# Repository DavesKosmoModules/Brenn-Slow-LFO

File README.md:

# Brenn-Slow-LFO

100mm Quad Slow LFO

- 4 Lfo's
- Each has a cycle duration between a few seconds and a few minutes, approx 6 sec 12 minutes
- Each LFO has it's own speed control
- A single global speed control
- CV control for the global speed (not 1V/Oct)
- Each LFO has both unipolar and bipolar outputs

I have been using the lfo for slow evolving movement of sounds, it is not a replacement for a standard lfo, normal tremolo
and vibrato can not be realized with this module.

It is based on the single cell VCO on the LM13700 datasheet, this is a triangle wave with a big step so I added
a LPF to each oscillator.

Contained are schematics & gerber files for pcb fabrication of both electrical aux and front panel. This is sutiable for entry level however a basic level of electronics, soldering, fault finding, and some basic tools are required.

[Schematic](/Docs/Brenn-Schematic.pdf)

[BOM](Docs/Brenn-BOM.pdf)

If you wish to edit in ki-cad the following dependencies are required

 https://github.com/holmesrichards/Kosmo_panel
 
 https://github.com/holmesrichards/aoKicad

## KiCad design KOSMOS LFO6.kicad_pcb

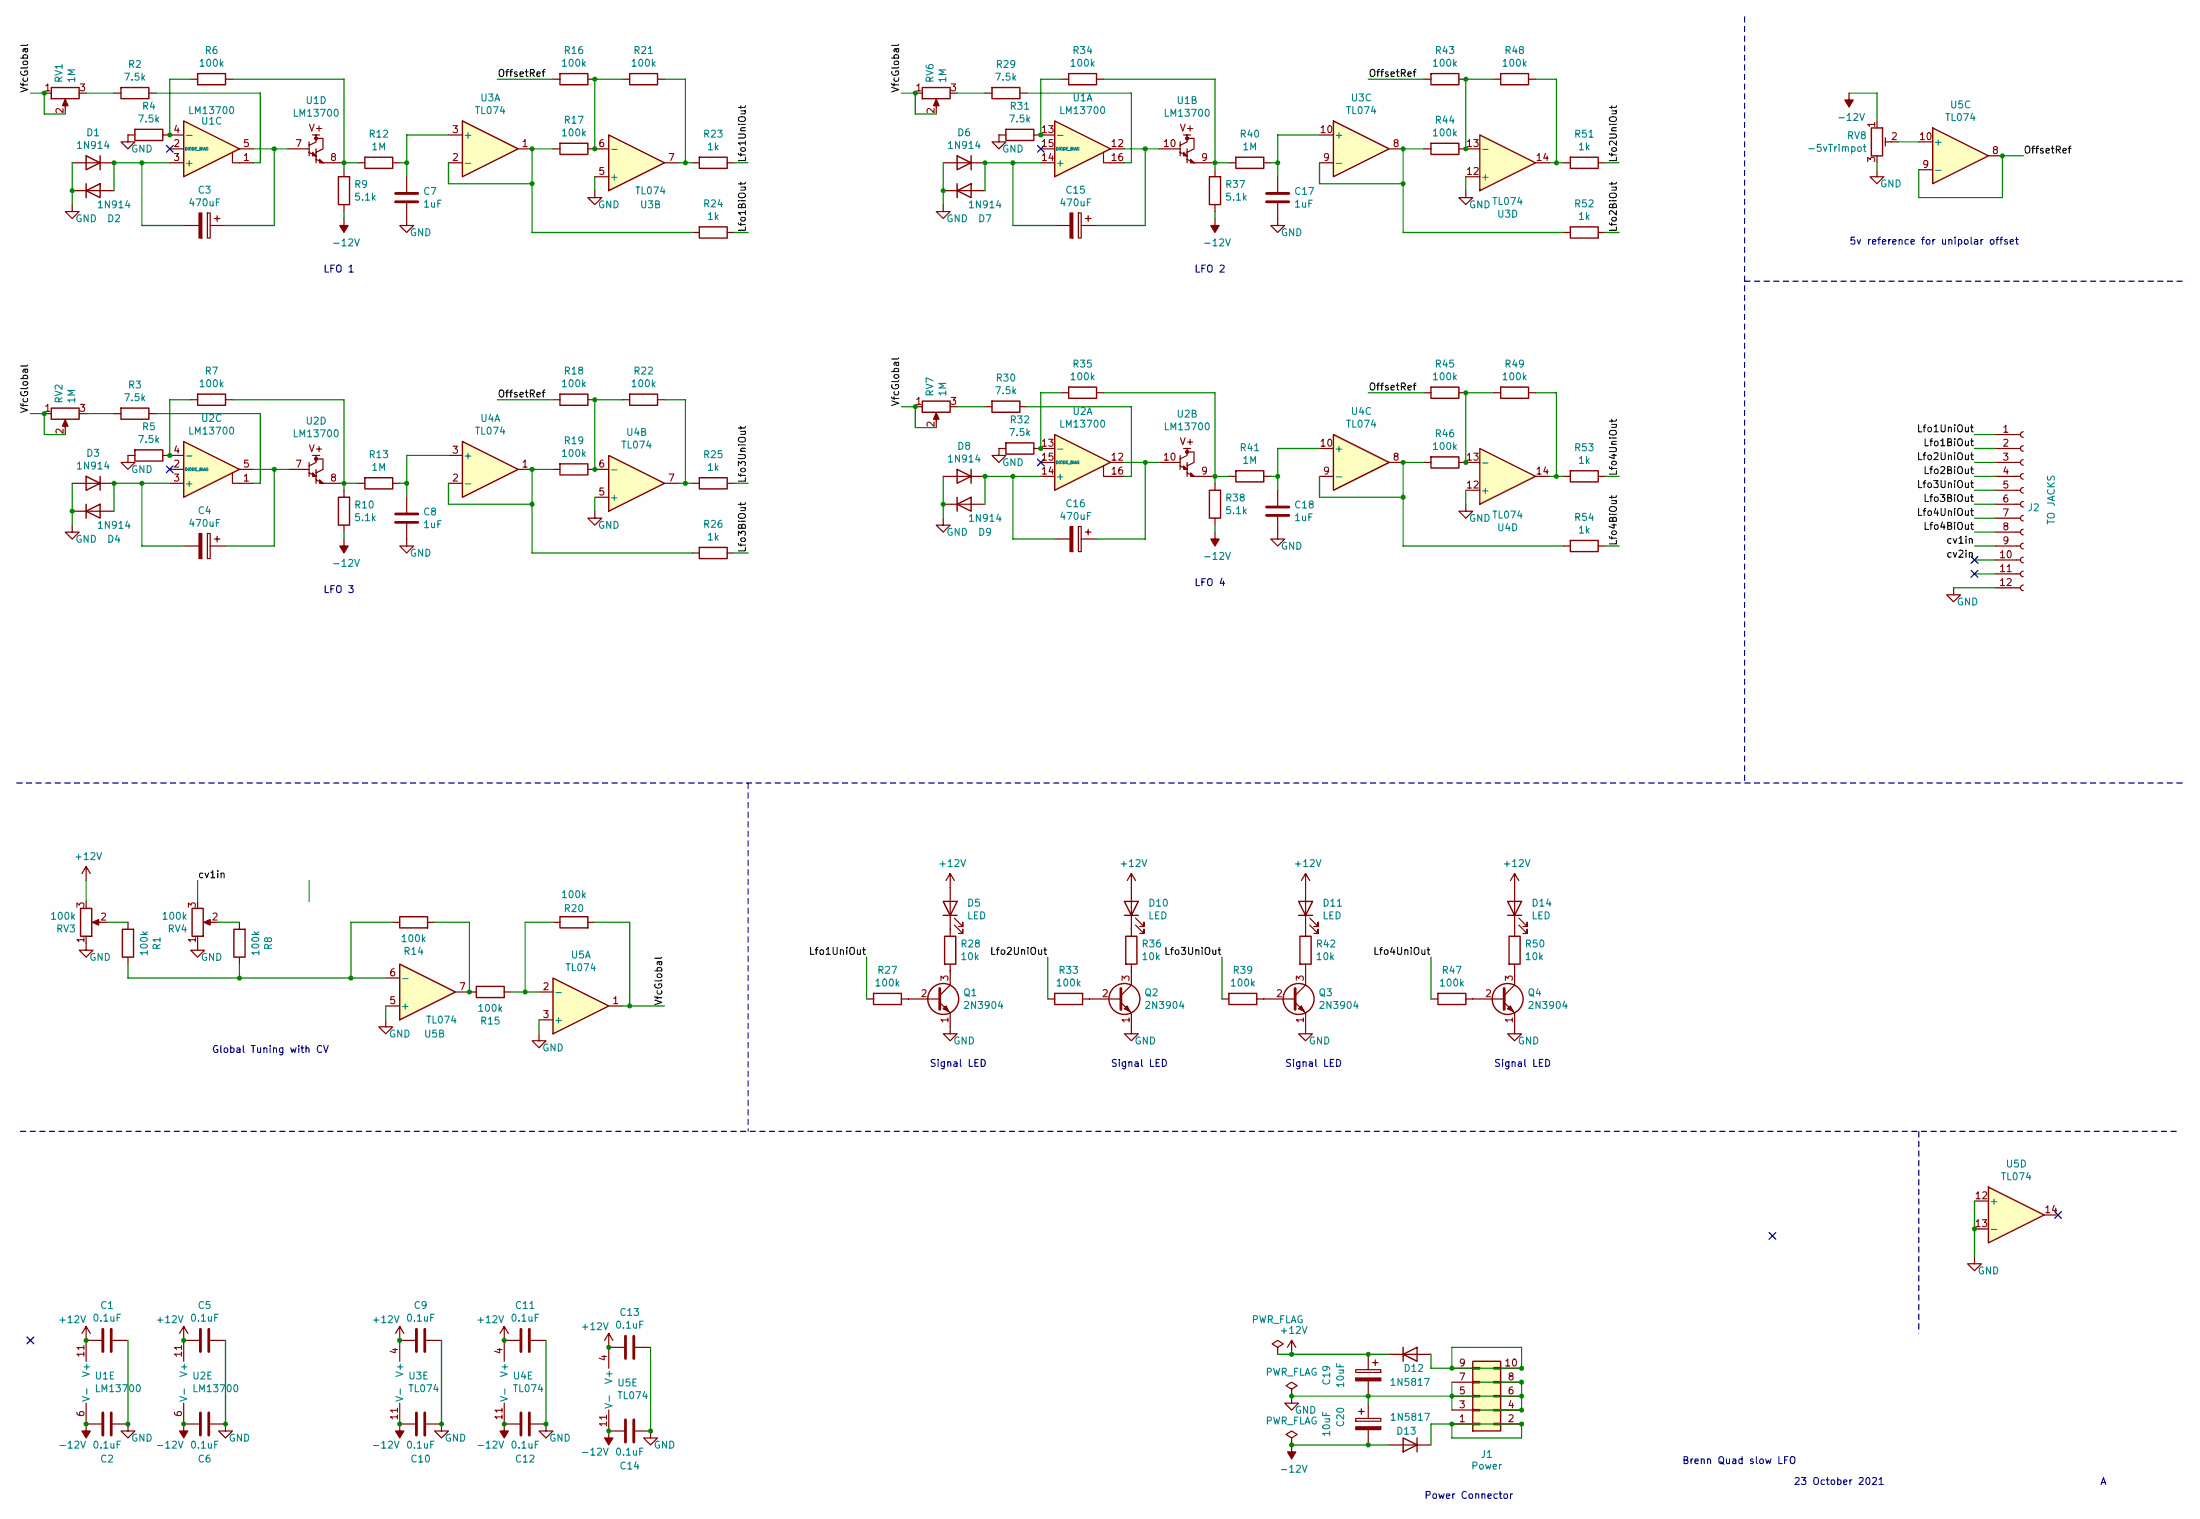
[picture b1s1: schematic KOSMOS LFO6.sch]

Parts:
C1, C2, C5, C6, C9, C10, C11, C12, C13, C14: 0.1uF; C_Disc_D6.0mm_W4.4mm_P5.00mm
C3, C4, C15, C16: 470uF; CP_Radial_D7.5mm_P2.50mm
C7, C8, C17, C18: 1uF; C_Disc_D6.0mm_W4.4mm_P5.00mm
C19, C20: 10uF; CP_Radial_D7.5mm_P2.50mm
D1, D2, D3, D4, D6, D7, D8, D9: 1N914; D_DO-35_SOD27_P7.62mm_Horizontal
D5, D10, D11, D14: LED; LED_D5.0mm
D12, D13: 1N5817; D_DO-41_SOD81_P12.70mm_Horizontal
J1: Power; IDC-Header_2x05_P2.54mm_Vertical
J2: TO JACKS; PinSocket_1x12_P2.54mm_Vertical
Q1, Q2, Q3, Q4: 2N3904; TO-92_Inline_Wide
R1, R6, R7, R8, R14, R15, R16, R17, R18, R19, R20, R21, R22, R27, R33, R34, R35, R39, R43, R44, R45, R46, R47, R48, R49: 100k; R_Axial_DIN0207_L6.3mm_D2.5mm_P10.16mm_Horizontal
R2, R3, R4, R5, R29, R30, R31, R32: 7.5k; R_Axial_DIN0207_L6.3mm_D2.5mm_P10.16mm_Horizontal
R9, R10, R37, R38: 5.1k; R_Axial_DIN0207_L6.3mm_D2.5mm_P10.16mm_Horizontal
R12, R13, R40, R41: 1M; R_Axial_DIN0207_L6.3mm_D2.5mm_P10.16mm_Horizontal
R23, R24, R25, R26, R51, R52, R53, R54: 1k; R_Axial_DIN0207_L6.3mm_D2.5mm_P10.16mm_Horizontal
R28, R36, R42, R50: 10k; R_Axial_DIN0207_L6.3mm_D2.5mm_P10.16mm_Horizontal
RV1, RV2, RV6, RV7: 1M; Potentiometer_Alpha_RD901F-40-00D_Single_Vertical_CircularH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
RV3, RV4: 100k; Potentiometer_Alpha_RD901F-40-00D_Single_Vertical_CircularH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
RV8: -5vTrimpot; Potentiometer_Bourns_3299W_Vertical
U1, U2: LM13700; DIP-16_W7.62mm_LongPads
U3, U4, U5: TL074; DIP-14_W7.62mm_LongPads

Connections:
+12V: C1.2, C5.2, C9.2, C11.2, C13.2, C19.1, D5.2 (A), D10.2 (A), D11.2 (A), D12.1 (K), D14.2 (A), RV3.3, U1.11 (V+), U2.11 (V+), U3.4 (V+), U4.4 (V+), U5.4 (V+)
-12V: C2.2, C6.2, C10.2, C12.2, C14.2, C20.2, D13.2 (A), R9.1, R10.1, R37.1, R38.1, RV8.1, U1.6 (V-), U2.6 (V-), U3.11 (V-), U4.11 (V-), U5.11 (V-)
/Lfo1BiOut: J2.2, R24.1
/Lfo1UniOut: J2.1, R23.1, R27.2
/Lfo2BiOut: J2.4, R52.1
/Lfo2UniOut: J2.3, R33.2, R51.1
/Lfo3BiOut: J2.6, R26.1
/Lfo3UniOut: J2.5, R25.1, R39.2
/Lfo4BiOut: J2.8, R54.1
/Lfo4UniOut: J2.7, R47.2, R53.1
/OffsetRef: R16.2, R18.2, R43.2, R45.2, U5.8, U5.9 (-)
/VfcGlobal: R20.2, RV1.1, RV1.2, RV2.1, RV2.2, RV6.1, RV6.2, RV7.1, RV7.2, U5.1
/cv1in: J2.9, RV4.3
/cv2in: J2.10
GND: C1.1, C2.1, C5.1, C6.1, C7.2, C8.2, C9.1, C10.1, C11.1, C12.1, C13.1, C14.1, C17.2, C18.2, C19.2, C20.1, D1.2 (A), D2.1 (K), D3.2 (A), D4.1 (K), D6.2 (A), D7.1 (K), D8.2 (A), D9.1 (K), J1.3, J1.4, J1.5, J1.6, J1.7, J1.8, J2.12, Q1.1 (E), Q2.1 (E), Q3.1 (E), Q4.1 (E), R4.2, R5.2, R31.2, R32.2, RV3.1, RV4.1, RV8.3, U3.5 (+), U3.12 (+), U4.5 (+), U4.12 (+), U5.3 (+), U5.5 (+), U5.12 (+), U5.13 (-)
unnamed: C3.1, U1.5, U1.7
unnamed: C3.2, D1.1 (K), D2.2 (A), U1.3 (+)
unnamed: C4.1, U2.5, U2.7
unnamed: C4.2, D3.1 (K), D4.2 (A), U2.3 (+)
unnamed: C7.1, R12.1, U3.3 (+)
unnamed: C8.1, R13.1, U4.3 (+)
unnamed: C15.1, U1.10, U1.12
unnamed: C15.2, D6.1 (K), D7.2 (A), U1.14 (+)
unnamed: C16.1, U2.10, U2.12
unnamed: C16.2, D8.1 (K), D9.2 (A), U2.14 (+)
unnamed: C17.1, R40.1, U3.10 (+)
unnamed: C18.1, R41.1, U4.10 (+)
unnamed: D5.1 (K), R28.1
unnamed: D10.1 (K), R36.1
unnamed: D11.1 (K), R42.1
unnamed: D12.2 (A), J1.9, J1.10
unnamed: D13.1 (K), J1.1, J1.2
unnamed: D14.1 (K), R50.1
unnamed: Q1.2 (B), R27.1
unnamed: Q1.3 (C), R28.2
unnamed: Q2.2 (B), R33.1
unnamed: Q2.3 (C), R36.2
unnamed: Q3.2 (B), R39.1
unnamed: Q3.3 (C), R42.2
unnamed: Q4.2 (B), R47.1
unnamed: Q4.3 (C), R50.2
unnamed: R1.1, R8.1, R14.1, U5.6 (-)
unnamed: R1.2, RV3.2
unnamed: R2.1, U1.1
unnamed: R2.2, RV1.3
unnamed: R3.1, U2.1
unnamed: R3.2, RV2.3
unnamed: R4.1, R6.2, U1.4 (-)
unnamed: R5.1, R7.2, U2.4 (-)
unnamed: R8.2, RV4.2
unnamed: R7.1, R10.2, R13.2, U2.8
unnamed: R6.1, R9.2, R12.2, U1.8
unnamed: R14.2, R15.1, U5.7
unnamed: R15.2, R20.1, U5.2 (-)
unnamed: R16.1, R17.1, R21.2, U3.6 (-)
unnamed: R17.2, R24.2, U3.1, U3.2 (-)
unnamed: R18.1, R19.1, R22.2, U4.6 (-)
unnamed: R19.2, R26.2, U4.1, U4.2 (-)
unnamed: R21.1, R23.2, U3.7
unnamed: R22.1, R25.2, U4.7
unnamed: R29.1, U1.16
unnamed: R29.2, RV6.3
unnamed: R30.1, U2.16
unnamed: R30.2, RV7.3
unnamed: R31.1, R34.2, U1.13 (-)
unnamed: R32.1, R35.2, U2.13 (-)
unnamed: R34.1, R37.2, R40.2, U1.9
unnamed: R35.1, R38.2, R41.2, U2.9
unnamed: R43.1, R44.1, R48.2, U3.13 (-)
unnamed: R44.2, R52.2, U3.8, U3.9 (-)
unnamed: R45.1, R46.1, R49.2, U4.13 (-)
unnamed: R46.2, R54.2, U4.8, U4.9 (-)
unnamed: R48.1, R51.2, U3.14
unnamed: R49.1, R53.2, U4.14
unnamed: RV8.2, U5.10 (+)

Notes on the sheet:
Power Connector
Signal LED
LFO 1
LFO 2
LFO 3
LFO 4
Global Tuning with CV
5v reference for unipolar offset
23 October 2021
Brenn Quad slow LFO

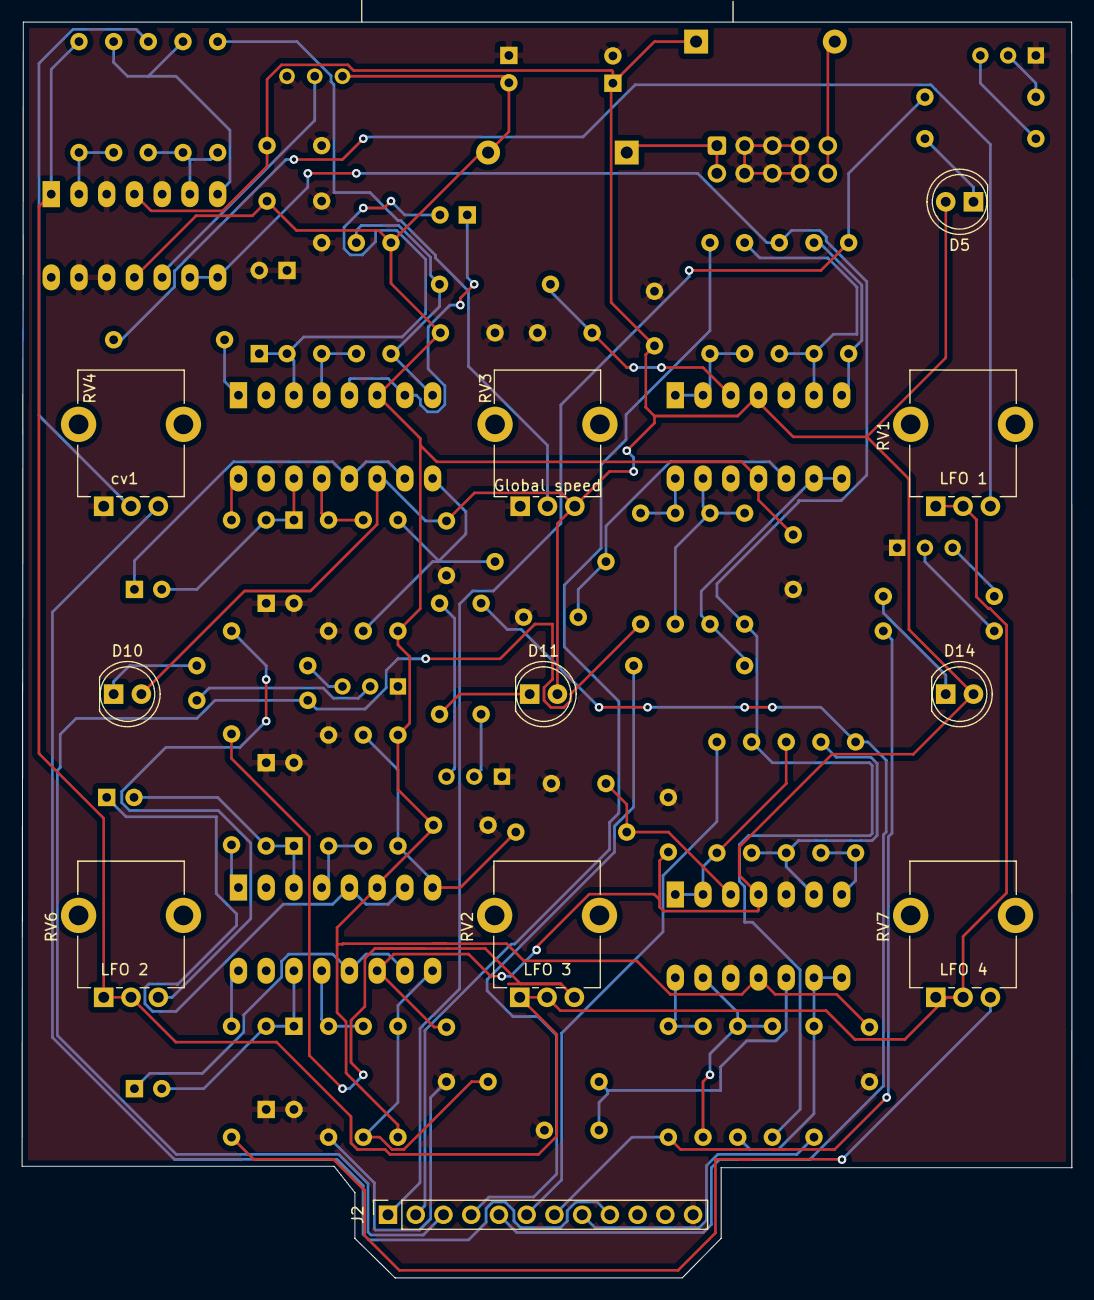
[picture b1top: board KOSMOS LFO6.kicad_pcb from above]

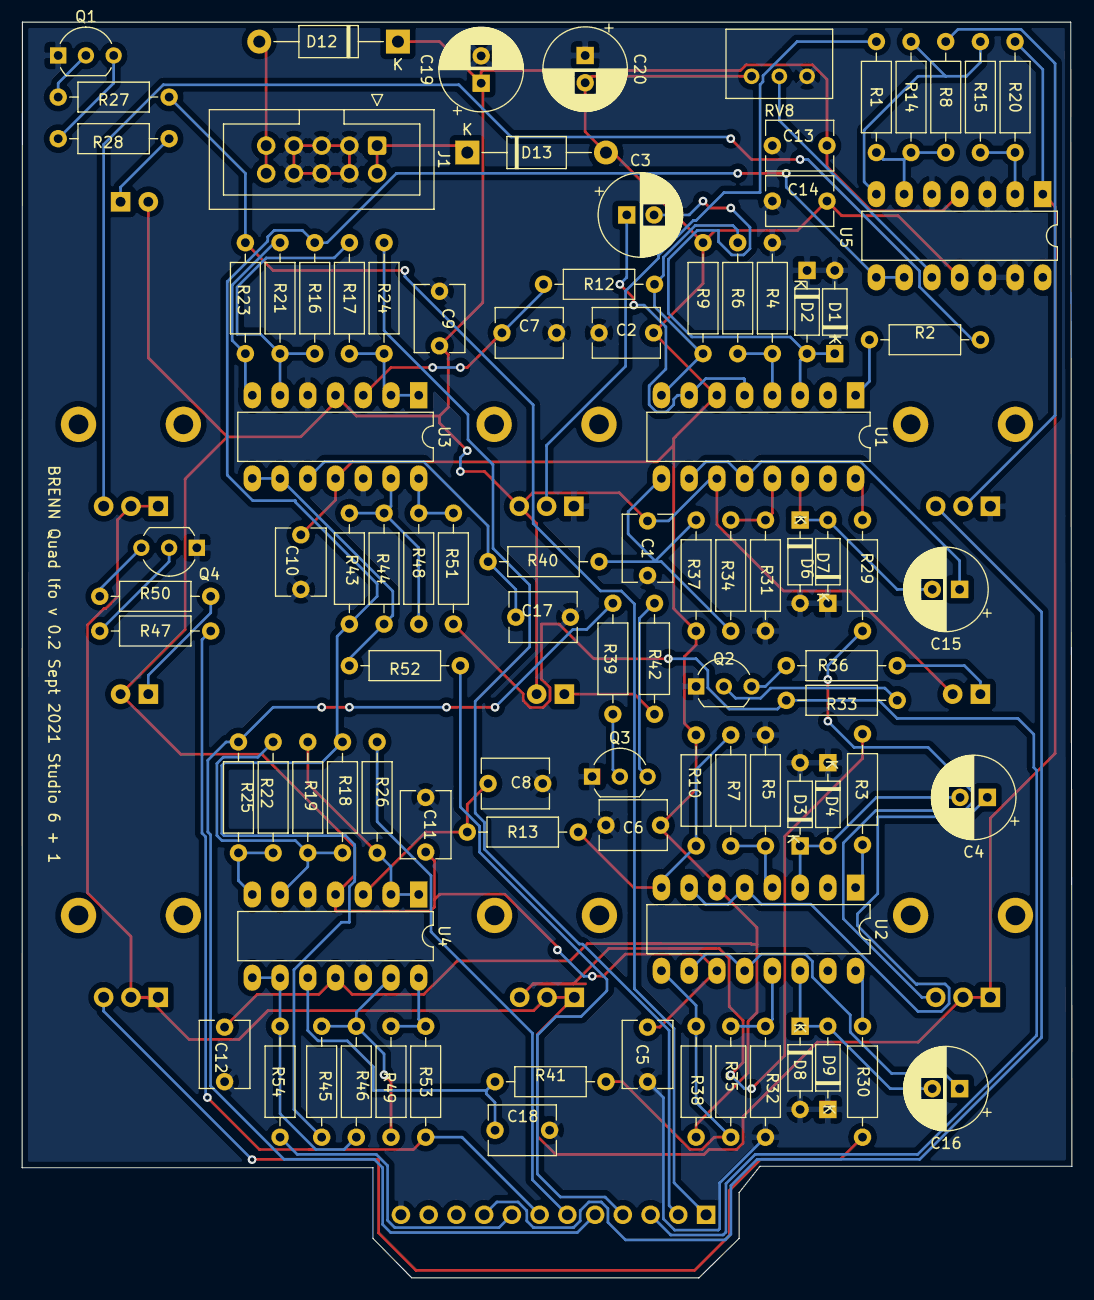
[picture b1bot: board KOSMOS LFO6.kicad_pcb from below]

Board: 2 copper layers, 96.1 x 115.0 mm, 105 parts (94 on the bottom side), 74 nets.

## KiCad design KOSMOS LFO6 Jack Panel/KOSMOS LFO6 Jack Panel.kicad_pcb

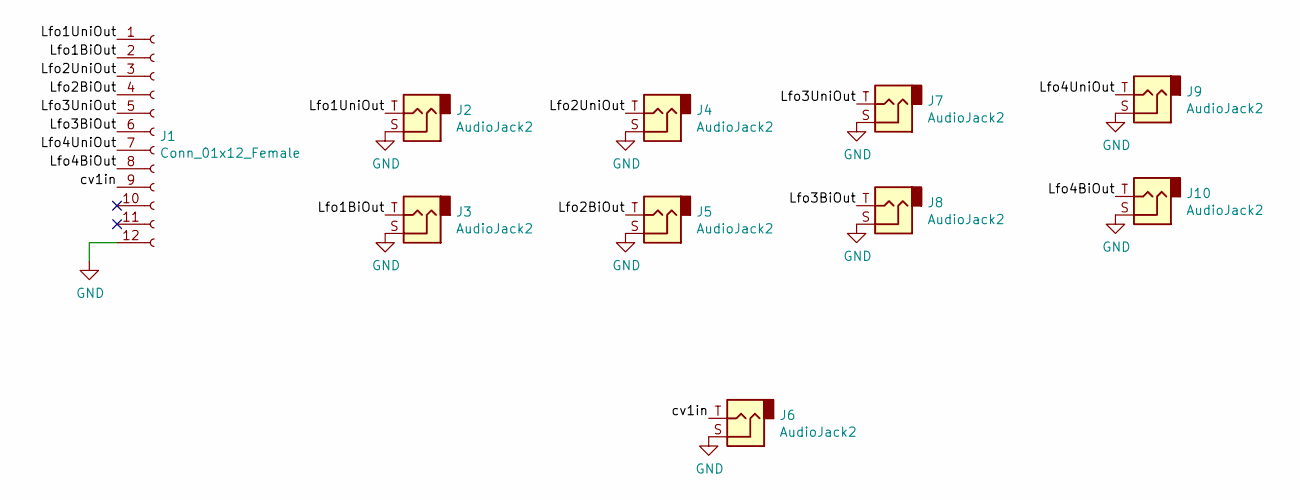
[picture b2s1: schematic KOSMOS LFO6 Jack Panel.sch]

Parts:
J1: Conn_01x12_Female; PinHeader_1x12_P2.54mm_Vertical
J2, J3, J4, J5, J6, J7, J8, J9, J10: AudioJack2; Jack_6.35mm_PJ_629HAN

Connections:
/Lfo1BiOut: J1.2, J3.T
/Lfo1UniOut: J1.1, J2.T
/Lfo2BiOut: J1.4, J5.T
/Lfo2UniOut: J1.3, J4.T
/Lfo3BiOut: J1.6, J8.T
/Lfo3UniOut: J1.5, J7.T
/Lfo4BiOut: J1.8, J10.T
/Lfo4UniOut: J1.7, J9.T
/cv1in: J1.9, J6.T
GND: J1.12, J2.S, J3.S, J4.S, J5.S, J6.S, J7.S, J8.S, J9.S, J10.S

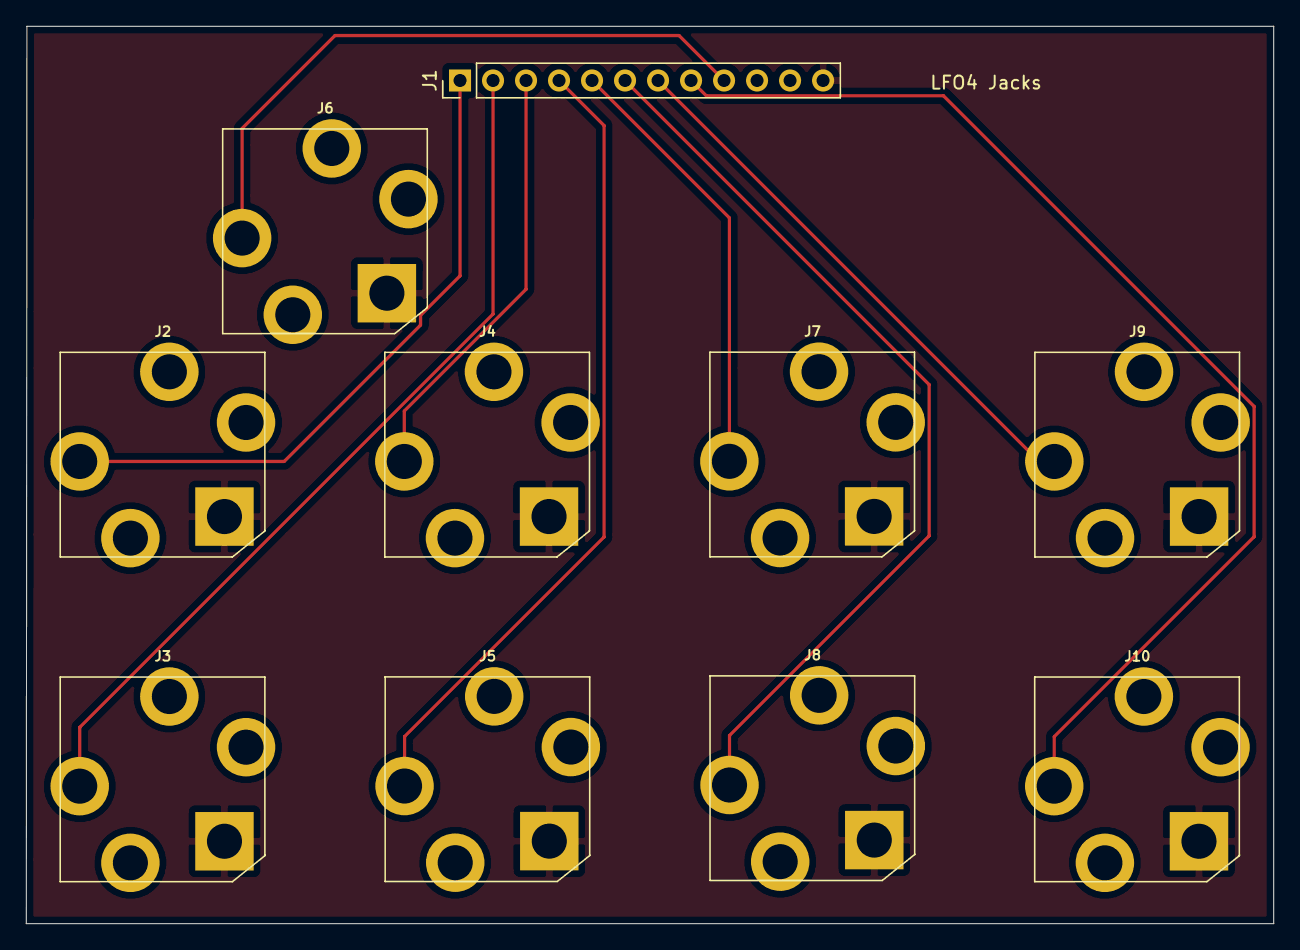
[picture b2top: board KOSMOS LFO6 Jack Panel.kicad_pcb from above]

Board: 2 copper layers, 96.0 x 69.1 mm, 10 parts (0 on the bottom side), 10 nets.

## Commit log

2021-10-23 Initial
2021-10-24 Readme spelling
